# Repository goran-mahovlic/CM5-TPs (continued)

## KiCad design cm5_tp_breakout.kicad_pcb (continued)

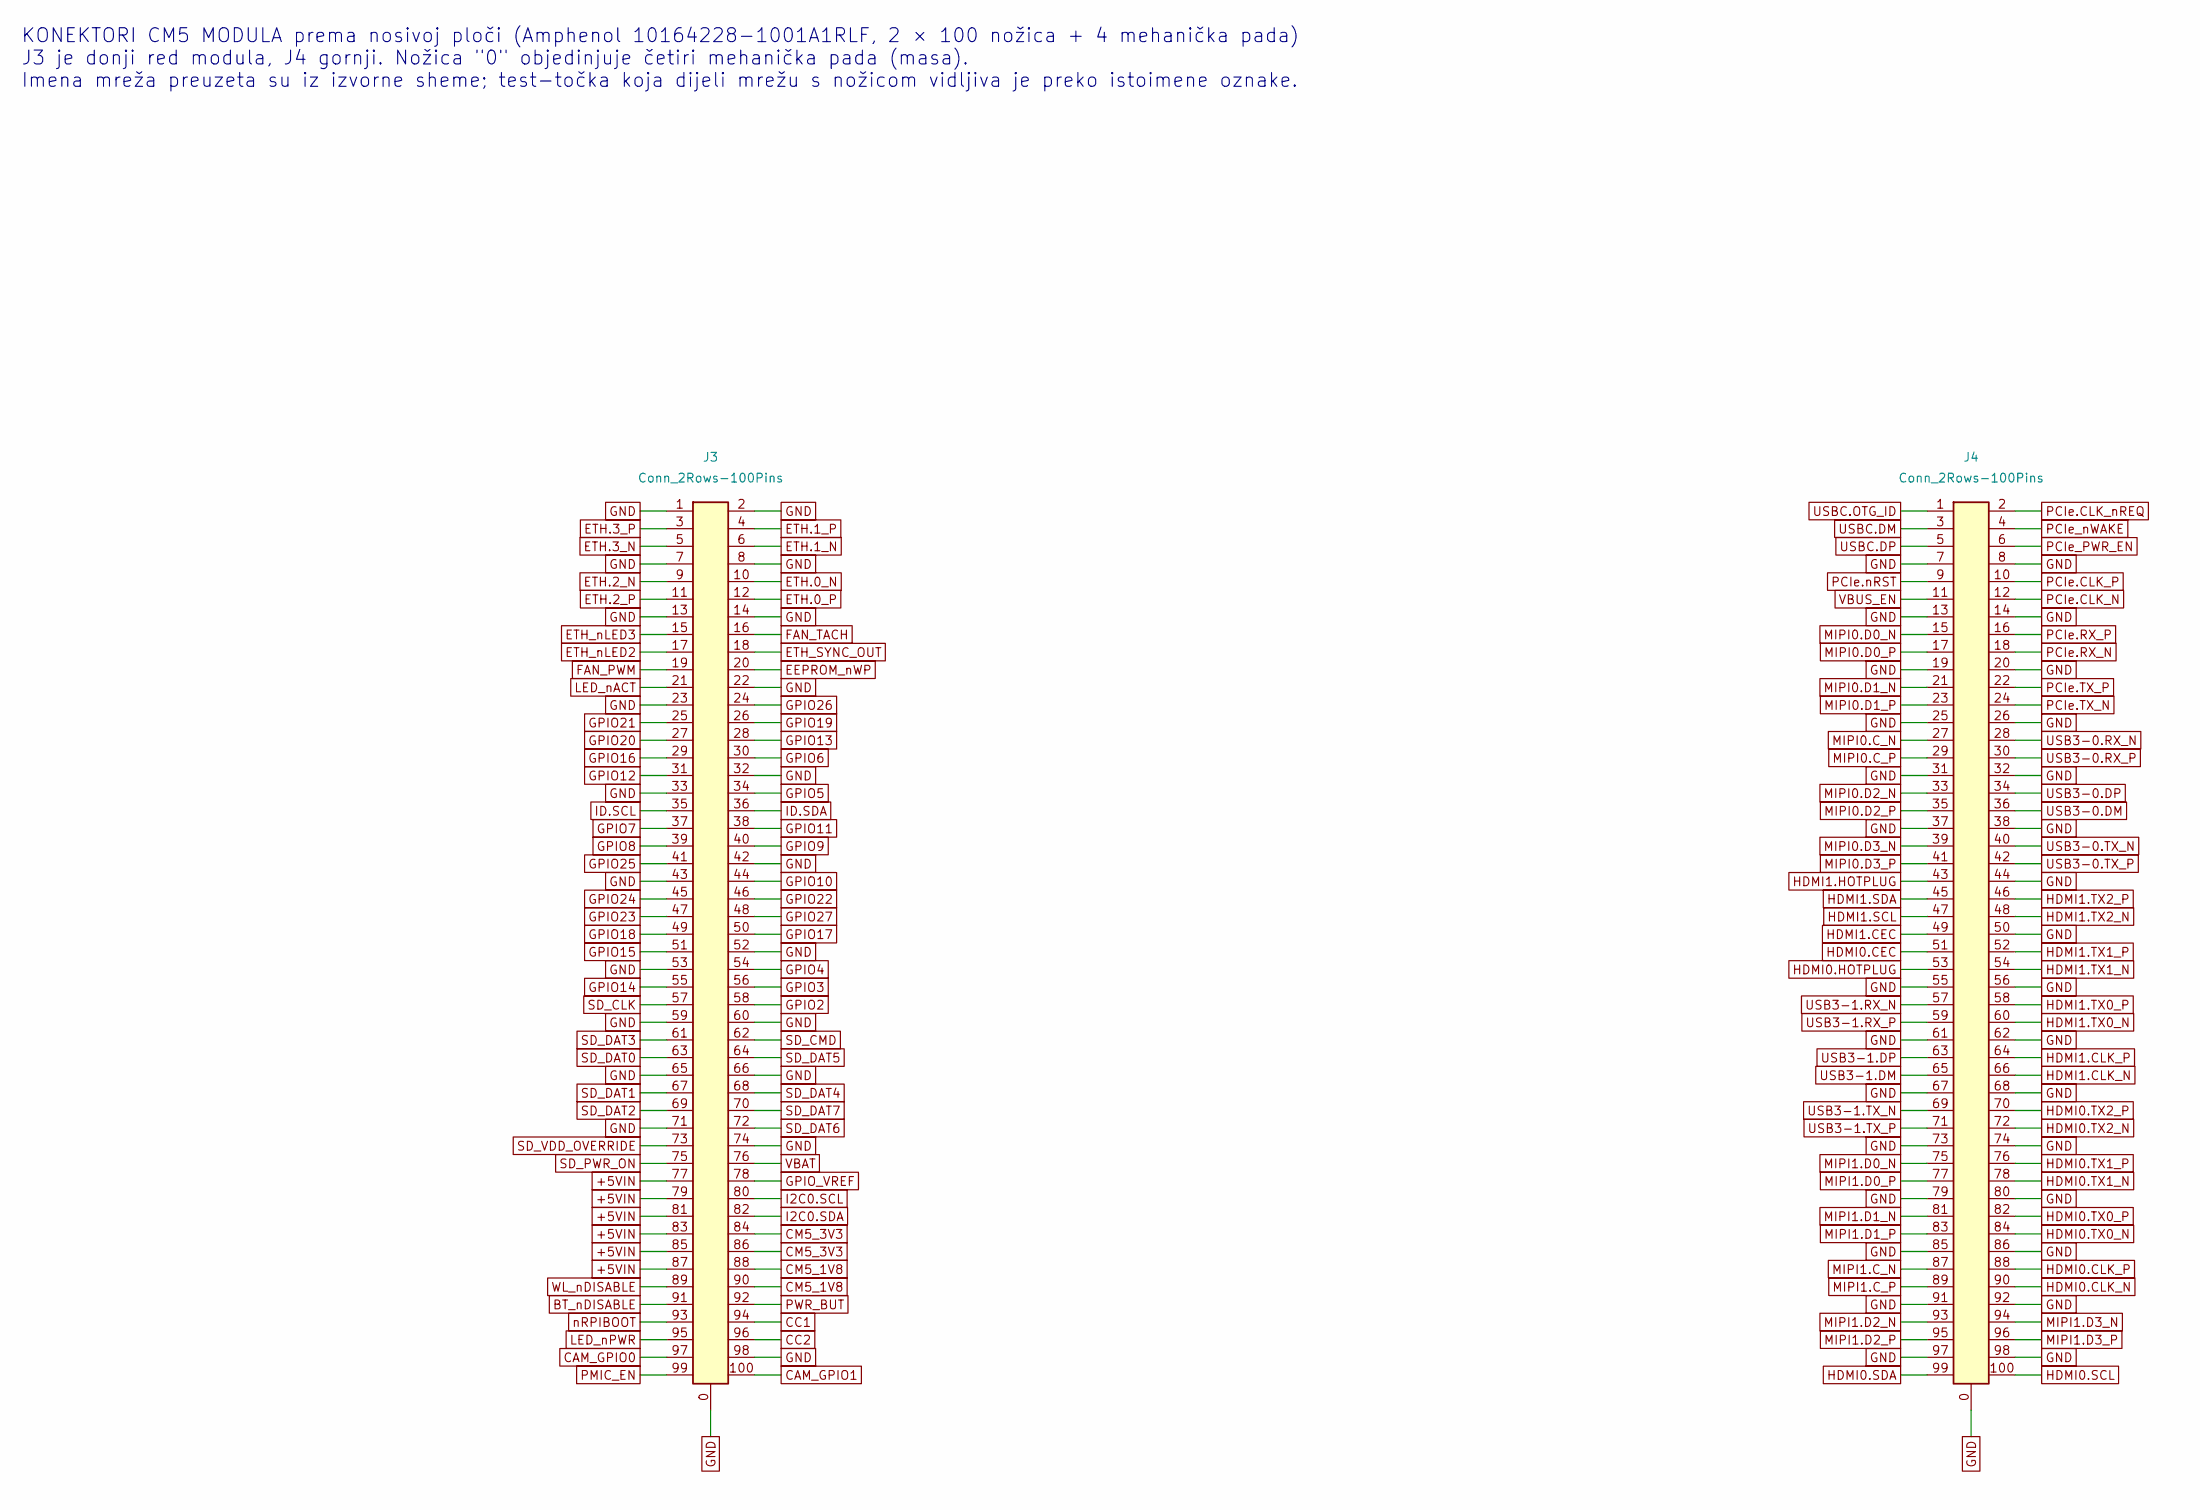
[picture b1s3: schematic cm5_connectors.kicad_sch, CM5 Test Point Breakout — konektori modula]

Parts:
J3, J4: Conn_2Rows-100Pins; 10164228-1001A1RLF

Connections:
+5VIN: J3.77, J3.79, J3.81, J3.83, J3.85, J3.87; also elsewhere on the board
BT_nDISABLE: J3.91
CAM_GPIO0: J3.97
CAM_GPIO1: J3.100
CC1: J3.94
CC2: J3.96
CM5_1V8: J3.88, J3.90; also elsewhere on the board
CM5_3V3: J3.84, J3.86; also elsewhere on the board
EEPROM_nWP: J3.20
ETH.0_N: J3.10; also elsewhere on the board
ETH.0_P: J3.12; also elsewhere on the board
ETH.1_N: J3.6; also elsewhere on the board
ETH.1_P: J3.4; also elsewhere on the board
ETH.2_N: J3.9; also elsewhere on the board
ETH.2_P: J3.11; also elsewhere on the board
ETH.3_N: J3.5; also elsewhere on the board
ETH.3_P: J3.3; also elsewhere on the board
ETH_SYNC_OUT: J3.18
ETH_nLED2: J3.17
ETH_nLED3: J3.15
FAN_PWM: J3.19
FAN_TACH: J3.16
GND: J3.0 (SH), J3.1, J3.2, J3.7, J3.8, J3.13, J3.14, J3.22, J3.23, J3.32, J3.33, J3.42, J3.43, J3.52, J3.53, J3.59, J3.60, J3.65, J3.66, J3.71, J3.74, J3.98, J4.0 (SH), J4.7, J4.8, J4.13, J4.14, J4.19, J4.20, J4.25, J4.26, J4.31, J4.32, J4.37, J4.38, J4.44, J4.50, J4.55, J4.56, J4.61, J4.62, J4.67, J4.68, J4.73, J4.74, J4.79, J4.80, J4.85, J4.86, J4.91, J4.92, J4.97, J4.98; also elsewhere on the board
GPIO2: J3.58
GPIO3: J3.56
GPIO4: J3.54
GPIO5: J3.34
GPIO6: J3.30
GPIO7: J3.37
GPIO8: J3.39
GPIO9: J3.40
GPIO10: J3.44
GPIO11: J3.38
GPIO12: J3.31
GPIO13: J3.28
GPIO14: J3.55
GPIO15: J3.51
GPIO16: J3.29
GPIO17: J3.50
GPIO18: J3.49
GPIO19: J3.26
GPIO20: J3.27
GPIO21: J3.25
GPIO22: J3.46
GPIO23: J3.47
GPIO24: J3.45
GPIO25: J3.41
GPIO26: J3.24
GPIO27: J3.48
GPIO_VREF: J3.78; also elsewhere on the board
HDMI0.CEC: J4.51
HDMI0.CLK_N: J4.90
HDMI0.CLK_P: J4.88
HDMI0.HOTPLUG: J4.53
HDMI0.SCL: J4.100
HDMI0.SDA: J4.99
HDMI0.TX0_N: J4.84
HDMI0.TX0_P: J4.82
HDMI0.TX1_N: J4.78
HDMI0.TX1_P: J4.76 (Pin_74)
HDMI0.TX2_N: J4.72
HDMI0.TX2_P: J4.70
HDMI1.CEC: J4.49
HDMI1.CLK_N: J4.66
HDMI1.CLK_P: J4.64
HDMI1.HOTPLUG: J4.43
HDMI1.SCL: J4.47
HDMI1.SDA: J4.45
HDMI1.TX0_N: J4.60
HDMI1.TX0_P: J4.58
HDMI1.TX1_N: J4.54
HDMI1.TX1_P: J4.52
HDMI1.TX2_N: J4.48
HDMI1.TX2_P: J4.46
I2C0.SCL: J3.80
I2C0.SDA: J3.82
ID.SCL: J3.35
ID.SDA: J3.36
LED_nACT: J3.21; also elsewhere on the board
LED_nPWR: J3.95; also elsewhere on the board
MIPI0.C_N: J4.27
MIPI0.C_P: J4.29
MIPI0.D0_N: J4.15
MIPI0.D0_P: J4.17
MIPI0.D1_N: J4.21
MIPI0.D1_P: J4.23
MIPI0.D2_N: J4.33
MIPI0.D2_P: J4.35
MIPI0.D3_N: J4.39
MIPI0.D3_P: J4.41
MIPI1.C_N: J4.87
MIPI1.C_P: J4.89
MIPI1.D0_N: J4.75
MIPI1.D0_P: J4.77
MIPI1.D1_N: J4.81
MIPI1.D1_P: J4.83
MIPI1.D2_N: J4.93
MIPI1.D2_P: J4.95
MIPI1.D3_N: J4.94
MIPI1.D3_P: J4.96
PCIe.CLK_N: J4.12
PCIe.CLK_P: J4.10
PCIe.CLK_nREQ: J4.2
PCIe.RX_N: J4.18
PCIe.RX_P: J4.16
PCIe.TX_N: J4.24
PCIe.TX_P: J4.22
PCIe.nRST: J4.9
PCIe_PWR_EN: J4.6
PCIe_nWAKE: J4.4
PMIC_EN: J3.99
PWR_BUT: J3.92; also elsewhere on the board
SD_CLK: J3.57
SD_CMD: J3.62
SD_DAT0: J3.63
SD_DAT1: J3.67
SD_DAT2: J3.69
SD_DAT3: J3.61
SD_DAT4: J3.68
SD_DAT5: J3.64
SD_DAT6: J3.72
SD_DAT7: J3.70
SD_PWR_ON: J3.75
SD_VDD_OVERRIDE: J3.73
USB3-0.DM: J4.36
USB3-0.DP: J4.34
USB3-0.RX_N: J4.28
USB3-0.RX_P: J4.30
USB3-0.TX_N: J4.40
USB3-0.TX_P: J4.42
USB3-1.DM: J4.65
USB3-1.DP: J4.63
USB3-1.RX_N: J4.57
USB3-1.RX_P: J4.59
USB3-1.TX_N: J4.69
USB3-1.TX_P: J4.71
USBC.DM: J4.3; also elsewhere on the board
USBC.DP: J4.5; also elsewhere on the board
USBC.OTG_ID: J4.1
VBAT: J3.76 (Pin_74)
VBUS_EN: J4.11
WL_nDISABLE: J3.89
nRPIBOOT: J3.93; also elsewhere on the board

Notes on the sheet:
KONEKTORI CM5 MODULA prema nosivoj ploči (Amphenol 10164228-1001A1RLF, 2 × 100 nožica + 4 mehanička pada) J3 je donji red modula, J4 gornji. Nožica "0" objedinjuje četiri mehanička pada (masa). Imena mreža preuzeta su iz izvorne sheme; test-točka koja dijeli mrežu s nožicom vidljiva je preko istoim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

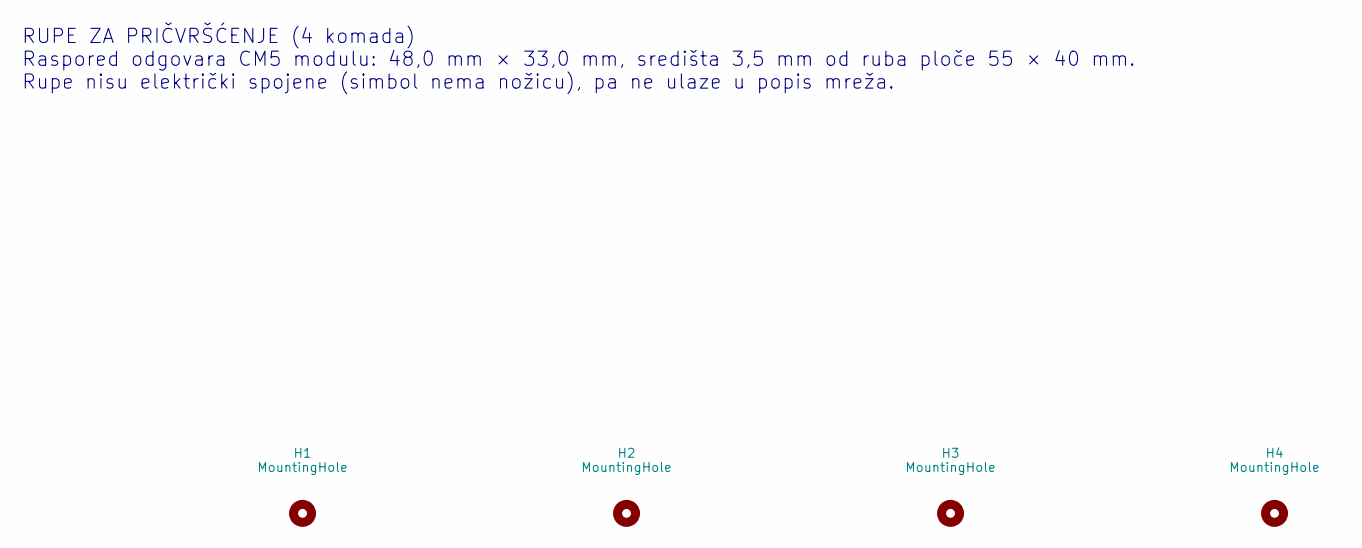
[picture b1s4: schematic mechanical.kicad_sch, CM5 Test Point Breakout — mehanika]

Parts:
H1, H2, H3, H4: MountingHole; CM5_MH

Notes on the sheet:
RUPE ZA PRIČVRŠĆENJE (4 komada) Raspored odgovara CM5 modulu: 48,0 mm × 33,0 mm, središta 3,5 mm od ruba ploče 55 × 40 mm. Rupe nisu električki spojene (simbol nema nožicu), pa ne ulaze u popis mreža.

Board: 2 copper layers, 64 parts (60 on the bottom side), 20 nets, no tracks yet.
